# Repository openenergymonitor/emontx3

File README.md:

# emonTx V3.4.x

## Documentation

- [Overview](https://docs.openenergymonitor.org/emontx3/overview.html)
- [Install Guide](https://docs.openenergymonitor.org/emontx3/install.html)
- [Adding to an existing install](https://docs.openenergymonitor.org/emontx3/add.html)
- [3 phase](https://docs.openenergymonitor.org/emontx3/3phase.html)
- [Add ESP8266](https://docs.openenergymonitor.org/emontx3/esp8266.html)
- [Direct Serial](https://docs.openenergymonitor.org/emontx3/direct.html)
- [Configuration](https://docs.openenergymonitor.org/emontx3/configuration.html)
- [Firmware](https://docs.openenergymonitor.org/emontx3/firmware.html)
- [Technical](https://docs.openenergymonitor.org/emontx3/technical.html)

This documentation can also be viewed on github directly [here](docs).

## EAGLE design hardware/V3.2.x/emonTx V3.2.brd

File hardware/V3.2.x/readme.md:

# emonTx 3.2.x

The emonTx v3.2 used the RFu328 module to provide both the ATmega328 and the RFM12B radio module. This was available pre-installed or the emonTx base board. 

## Port Map

*Note: pulse counting on IRQ0, Dig2 rather than IRQ1 Dig3 on the emonTx3.4 

## Firmware

See: [https://github.com/openenergymonitor/emonTxFirmware/tree/master/emonTxV3/RFM/emonTxV3.2 ](https://github.com/openenergymonitor/emonTxFirmware/tree/master/emonTxV3/RFM/emonTxV3.2 )

## RF Connectivity

### RFM12B

To use the RFM12B on the RFu328, a modified version of the JeeLib RF12 library has been created. This is called the [RFu_JeeLib](https://github.com/openenergymonitor/RFu_jeelib) see the GitHub readme for details regarding the modifications. 

The emonTx V3.2 was initially shipped with a wire whip antenna. An SMA antenna could alternatively be added by soldering in the connector on the board. A small wire link was required between the RFu328 and the base board if an RFu328 with headers was used. See [EmonTx_V3_SMA.jpg](img/EmonTx_V3_SMA.jpg) & [EmonTx_V3_SMA_RFu_headers.jpg](img/EmonTx_V3_SMA_RFu_headers.jpg).

Power consumption:

- MCU sleep + RFM12B sleep: 0.034 mA
- MCU running: 7.3mA 
- MCU + LED: 9-10mA
- RFM12B TX ~3ms: 23-28mA

### RF testing

All antennas and RFM12B modules were 433MHz running standard emonTx discrete sampling firmware, transmitting once very 10s.

An RFM69CW receiver provided RSSI readings to enable antenna comparison. The RSSI readings were all lower than normal since the RFM69CW used is an 868MHz module, with an 868MHz antenna, forced via software, to a 433MHz receive frequency.

The emonTxs with the SMA antenna had the RFu328 soldered directly (SMT) to the PCB, the coil and whip antenna had the RFu328 mounted using headers 

## BOM

## Dimensions

Enclosure: extruded aluminium case with acrylic fascia.

**DIN Rail Mount:** Thanks to [@Aquefot](http://twitter.ccom/Aquefot) for contributing a [DIN mount rail fitting CAD design](https://twitter.com/aquefot/status/413708371809026048/photo/1) ready to be 3D printed for the emonTx: [Thingiverse Download](http://www.thingiverse.com/thing:208177) 

## Licence

Creative Commons Attribution-ShareAlike 3.0 Unported License

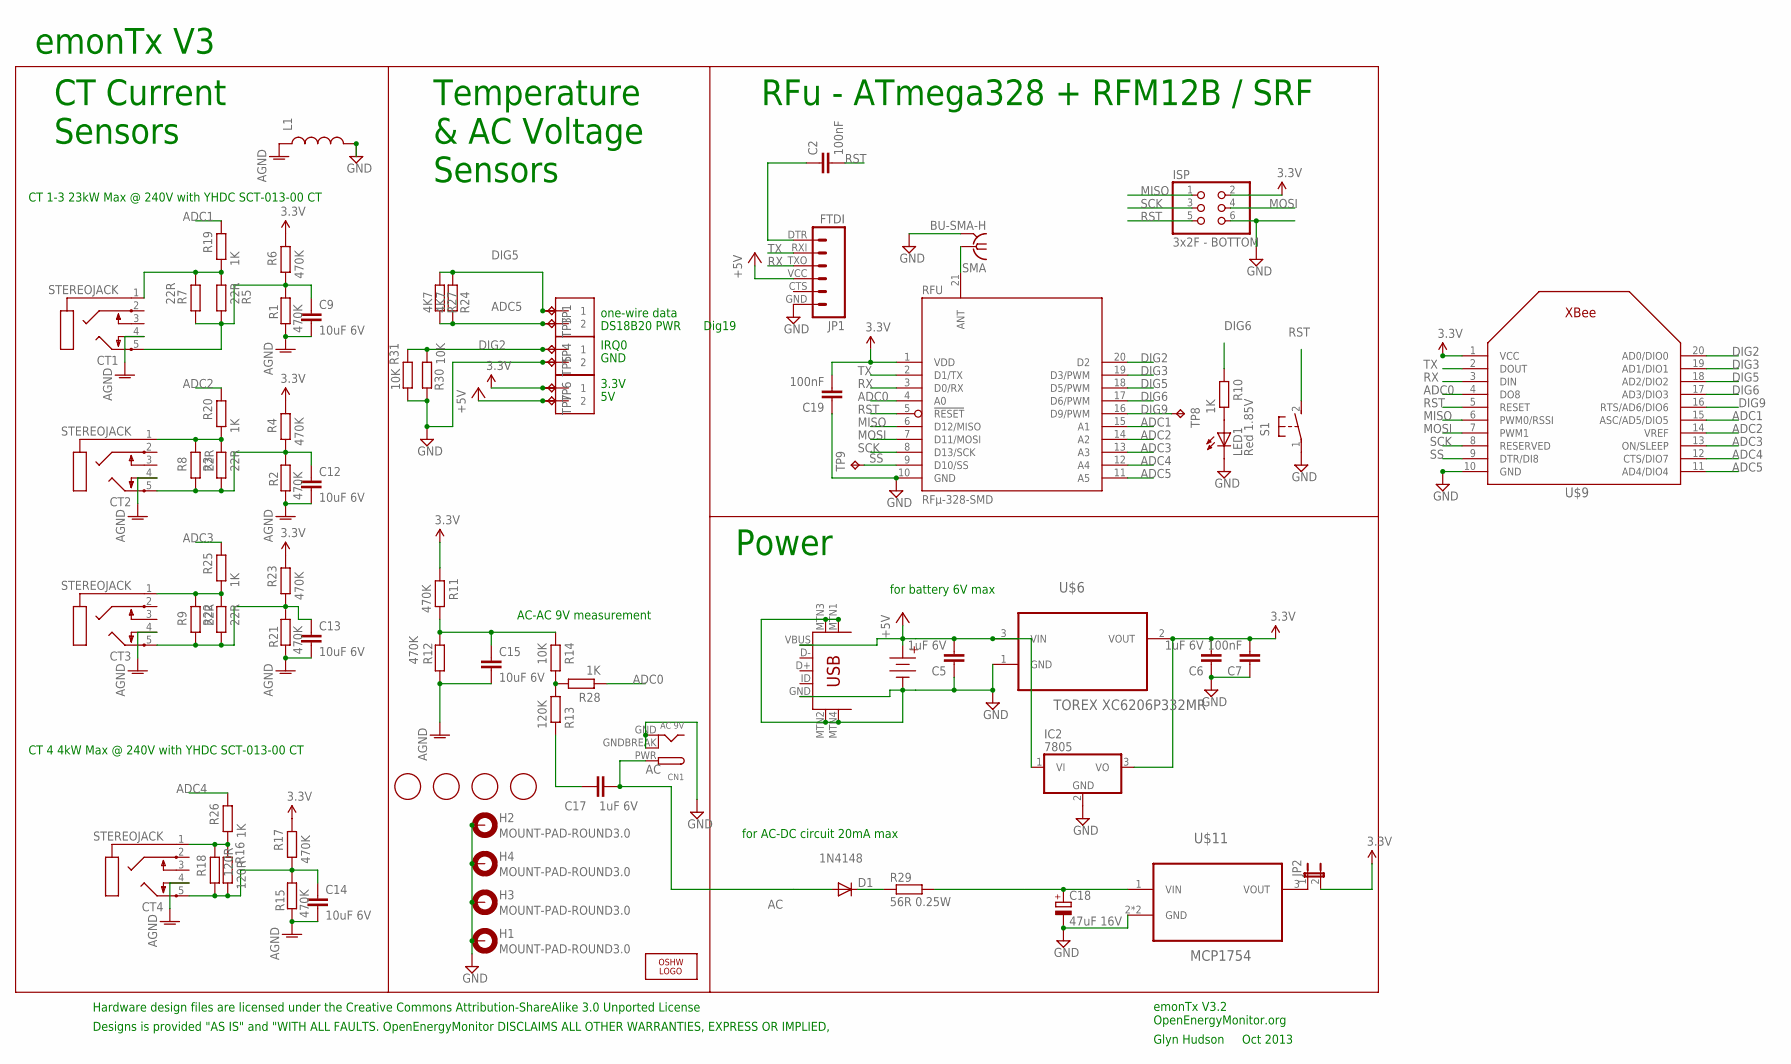
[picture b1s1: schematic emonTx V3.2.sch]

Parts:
C2, C7, C19: 100nF; C0603
C5, C6, C17: 1uF 6V; C0603
C9, C12, C13, C14, C15: 10uF 6V; C0603
C18: 47uF 16V; PANASONIC_D
CN1: AC 9V; DCJACK_2MM_PTH
CT1, CT2, CT3, CT4: STEREOJACK; STX3100
D1: 1N4148; SOD-323
H1, H2, H3, H4: MOUNT-PAD-ROUND3.0; 3,0-PAD
IC2: 7805; TO220V
ISP: 3x2F - BOTTOM; 2X03
J1, J2, J4: 1X2-3.5MM
JP1: FTDI; FTDI_BASIC
JP2: JUMPER-2PTH_LOCK; 1X02_LOCK
L1: INDUCTOR0603; 0603
LED1: Red 1.85V; CHIP-LED0805
LOGO1: OSHW_LOGO_6MILX0200-NT; OSHW_6X200_NOTEXT
R1, R2, R4, R6, R11, R12, R15, R17, R21, R23: 470K; R0603
R3, R5, R22: 22R; 0204/7
R7, R8, R9: 22R; R1206
R10, R19, R20, R25, R26, R28: 1K; R0603
R13: 120K; R0603
R14, R31: 10K; R0603
R16: 120R; 0204/7
R18: 120R; R1206
R24: 4K7; 0204/7
R27: 4K7; R0603
R29: 56R 0.25W; R1206
R30: 10K; 0204/7
RFU: RFµ-328-SMD; RFµ-328-LANDING
S1: 31-XX; B3F-31XX
SMA: BU-SMA-H
TP1, TP3, TP4, TP5, TP6, TP7, TP8, TP9: TPPAD1-13; P1-13
U$1, U$4, U$5, U$7: FIDUCIAL; FIDUCIAL_1MM
U$3: 4.5V; AAA_PCB_HOLDER
U$6: TOREX XC6206P332MR; SOT95P237X112-3N
U$9: XBEE
U$10: USB-MINIB-5PIN; USB-MINIB-CISECO
U$11: MCP1754; SOT89

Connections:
3.3V: C6.2, C7.2, C19.2, IC2.3 (VO), ISP.2, J4.1, JP2.2, R4.2, R6.2, R11.2, R17.2, R23.2, RFU.1 (VDD), TP6.TP, U$6.2 (VOUT), U$9.1 (VCC)
+5V: C5.2, IC2.1 (VI), J4.2, JP1.VCC (4), TP7.TP, U$3.+, U$6.3 (VIN), U$10.VBUS
AC: C17.2, CN1.PWR, D1.2 (A)
ADC0: R28.1, RFU.4 (A0), U$9.4 (DO8)
ADC1: R19.2, RFU.15 (A1), U$9.15 (ASC/AD5/DIO5)
ADC2: R20.2, RFU.14 (A2), U$9.14 (VREF)
ADC3: R25.2, RFU.13 (A3), U$9.13 (ON/SLEEP)
ADC4: R26.2, RFU.12 (A4), U$9.12 (CTS/DIO7)
ADC5: J2.2, R24.2, R27.2, RFU.11 (A5), TP3.TP, U$9.11 (AD4/DIO4)
AGND: C9.2, C12.2, C13.2, C14.2, C15.2, CT1.4, CT2.4, CT3.4, CT4.4, L1.1, R1.2, R2.2, R12.1, R15.2, R21.2
DIG2: J1.1, R30.1, R31.1, RFU.20 (D2), TP4.TP, U$9.20 (AD0/DIO0)
DIG3: RFU.19 (D3/PWM), U$9.19 (AD1/DIO1)
DIG5: J2.1, R24.1, R27.1, RFU.18 (D5/PWM), TP1.TP, U$9.18 (AD2/DIO2)
DIG6: R10.2, RFU.17 (D6/PWM), U$9.17 (AD3/DIO3)
DIG9: RFU.16 (D9/PWM), TP8.TP, U$9.16 (RTS/AD6/DIO6)
GND: C5.1, C6.1, C7.1, C18.-, C19.1, CN1.GND, CN1.GNDBREAK, H1.B3,0, H2.B3,0, H3.B3,0, H4.B3,0, IC2.2 (GND), ISP.6, J1.2, JP1.GND (6), L1.2, LED1.C, R30.2, R31.2, RFU.10 (GND), S1.1, SMA.2, SMA.3 (2), SMA.4 (2), SMA.5 (2), TP5.TP, U$3.-, U$6.1 (GND), U$9.10 (GND), U$10.GND, U$10.MTN1 (MTN2), U$10.MTN2 (MTN3), U$10.MTN3 (MTN1), U$10.MTN4, U$11.2 (GND), U$11.2.1 (GND)
MISO: ISP.1, RFU.6 (D12/MISO), U$9.6 (PWM0/RSSI)
MOSI: ISP.4, RFU.7 (D11/MOSI), U$9.7 (PWM1)
unnamed: CT1.1, R5.2, R7.2, R19.1
unnamed: C13.1, CT3.5, R9.1, R21.1, R22.1, R23.1
unnamed: R13.2, R14.1, R28.2
unnamed: JP2.1, U$11.3 (VOUT)
unnamed: C18.+, R29.2, U$11.1 (VIN)
unnamed: C17.1, R13.1
unnamed: CT4.1, R16.2, R18.2, R26.1
unnamed: C2.1, JP1.DTR (1)
unnamed: CT2.1, R3.2, R8.2, R20.1
unnamed: RFU.21 (ANT), SMA.1
unnamed: D1.1 (C), R29.1
unnamed: CT3.1, R9.2, R22.2, R25.1
unnamed: C12.1, CT2.5, R2.1, R3.1, R4.1, R8.1
unnamed: C15.1, R11.1, R12.2, R14.2
unnamed: C14.1, CT4.5, R15.1, R16.1, R17.1, R18.1
unnamed: C9.1, CT1.5, R1.1, R5.1, R6.1, R7.1
unnamed: LED1.A, R10.1
RST: C2.2, ISP.5, RFU.5 (!RESET), S1.2 (S), U$9.5 (RESET)
RX: JP1.TXO (3), RFU.3 (D0/RX), U$9.3 (DIN)
SCK: ISP.3, RFU.8 (D13/SCK), U$9.8 (RESERVED)
SS: RFU.9 (D10/SS), TP9.TP, U$9.9 (DTR/DI8)
TX: JP1.RXI (2), RFU.2 (D1/TX), U$9.2 (DOUT)

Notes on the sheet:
AC-AC 9V measurement
emonTx V3.2 OpenEnergyMonitor.org
Glyn Hudson Oct 2013
CT 4 4kW Max @ 240V with YHDC SCT-013-00 CT
CT 1-3 23kW Max @ 240V with YHDC SCT-013-00 CT
for battery 6V max
for AC-DC circuit 20mA max
Dig19
Power
RFu - ATmega328 + RFM12B / SRF
CT Current Sensors
Temperature & AC Voltage Sensors
Designs is provided "AS IS" and "WITH ALL FAULTS. OpenEnergyMonitor DISCLAIMS ALL OTHER WARRANTIES, EXPRESS OR IMPLIED,
Hardware design files are licensed under the Creative Commons Attribution-ShareAlike 3.0 Unported License
emonTx V3
DS18B20 PWR
one-wire data
IRQ0
GND
3.3V

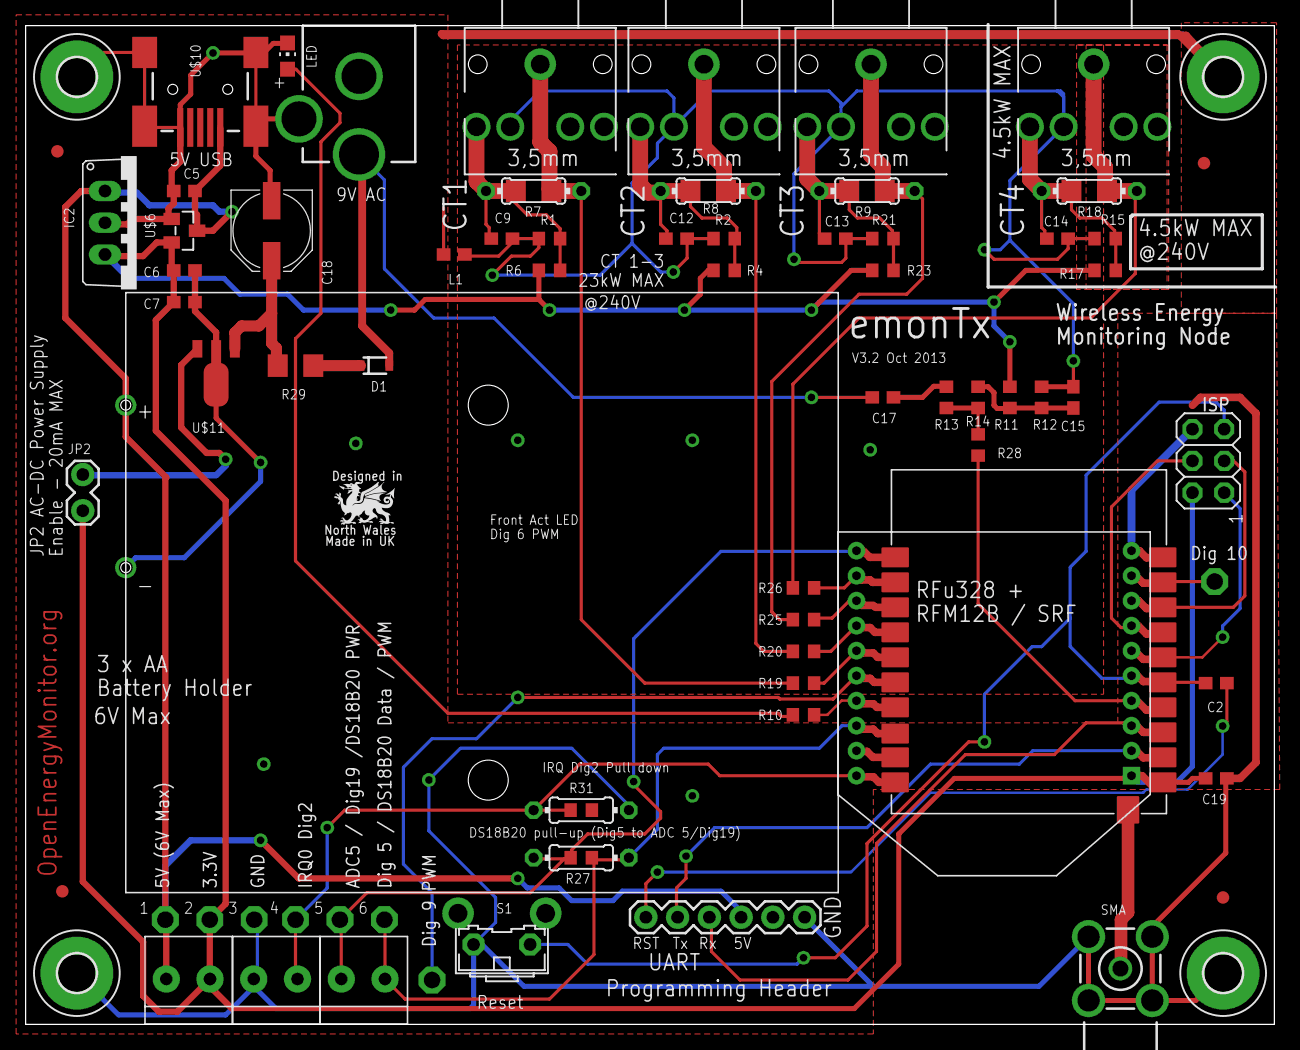
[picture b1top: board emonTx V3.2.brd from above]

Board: 2 copper layers, 99.9 x 79.9 mm, 83 parts (1 on the bottom side), 40 nets.

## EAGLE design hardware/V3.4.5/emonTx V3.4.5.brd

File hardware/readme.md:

# emonTx V3.4

The emonTx V3.4 is the latest generation of the open-source hardware Arduino compatiable emonTx low power wireless energy monitoring node. The unit has been totally re-designed using surface mount (SMT) electronics to enable automated pre-assembled manufacture here in the UK.

## Hardware change log

### V3.4.5 

*Not yet released as of April 2021*

PCB changes
- Remove MLF ATmega footprint to avoid solder bridges during reflow
- Fix rear silkscreen version number
- Improve via spacing 

BOM changes
- Update R13 & R14 from 1% to 0.5% tolerance
- Switch to LDK320ADU33R LDO for higher 18V input voltage
- Remove battery holder from BOM 
- Revert to 4x 3.5mm black CT sockets due to procurement issues for differnet colour sockets
- Moved TSV diodes from ESD5Z3.3T1G to UCLAMP3301H to procurement issues 

### V3.4.4 

Minor PCB changes:

- fix overlayed double via
- Add protection ring for top-right fiducial

### V3.4.3

**Shipping March/April 2018 onwards**

- Identifiable with blue CT4 jackplug socket (mostly)
- Add extra UART header with Rx/Tx swap-over for easy ESP connection
- Increase  reservoir capacitor of AC-DC circuit C18 16uF to 100uF to allow for greater peak power consumption of RFM69CW (compared to RFM12B)
- Change Burden resistors R7, R8, R9 (22R) from 1% to 0.5% tolerance  to increase accuracy. Wanted to change to 0.1% but unable to source
- Changed Burden resistor R18 (120R) from 1 % to 0.1%
- Change all 470K resistors from 1% to 0.1% (R1, R2, R4, R6, R11, R12, R15, R17, R21, R23, R27, R30)
- Changed CT4 jack plug socket to blue colour to indicate low power high accuracy channel

Live BOM: https://octopart.com/bom-tool/xiwE7CiN

#### V3.4.2

**Aug 2016**

- Same BOM as V3.4.1
- Increase mini USB location pin holes from 0.8mm to 0.9mm

#### 3.4.1 Mar 2015

- lots of via GND links around GND plane - make sure ant has best GND plane possible
- make sure antenna has got GND plane under ant PCB trace
- pull top gnd plane in around RFM69CW module and rear GND plan to cover whole undersided
- Get rid of unused L1
- Move D2 location to not be under battery holder
- Correct terminal block silkscreen
- Disconnect RJ45 pin 1 and 3 from GND, stop power rail short if ethernet cable is connected by mistake

#### V3.4

- More FTDI connection bit to the left
- Increase pads for DIP switch
- Add TVS diodes, CT input protection

### V3.3

- ATmega328 on-board
- Edge SMA Antenna
- Non plate through mounting pads to eliminate interference through enclosure
- RJ45 DS18B20 temperature sensor
- 3 x AA Battery monitor on ADC7
- DIP Switch on Dig8 and Dig9 for Node ID selection
- RFM69CW compatible with SEL line pull-up resistor
- Pulse counting / terminal block IRQ changed from D2 IRQ0 to D3 IRQ1 since RFM12B now uses IRQ0
- Changed MCP1700 3.3V regulator to MCP1702 3.3V regulator to allow for powering from higher voltages (12V max) over RJ45

***

## Links

- [Purchase](http://shop.openenergymonitor.com/emontx-v3/)

- [User Guide](https://guide.openenergymonitor.org/setup/emontx)

***

### Schematic

### Board

## Portmap

### Open Hardware

Hardware designs (schematics and CAD) files are licensed under the [Creative Commons Attribution-ShareAlike 3.0 Unported License](http://creativecommons.org/licenses/by-sa/3.0/) and follow the terms of the [OSHW (Open-source hardware) Statement of Principles 1.0.](http://freedomdefined.org/OSHW)

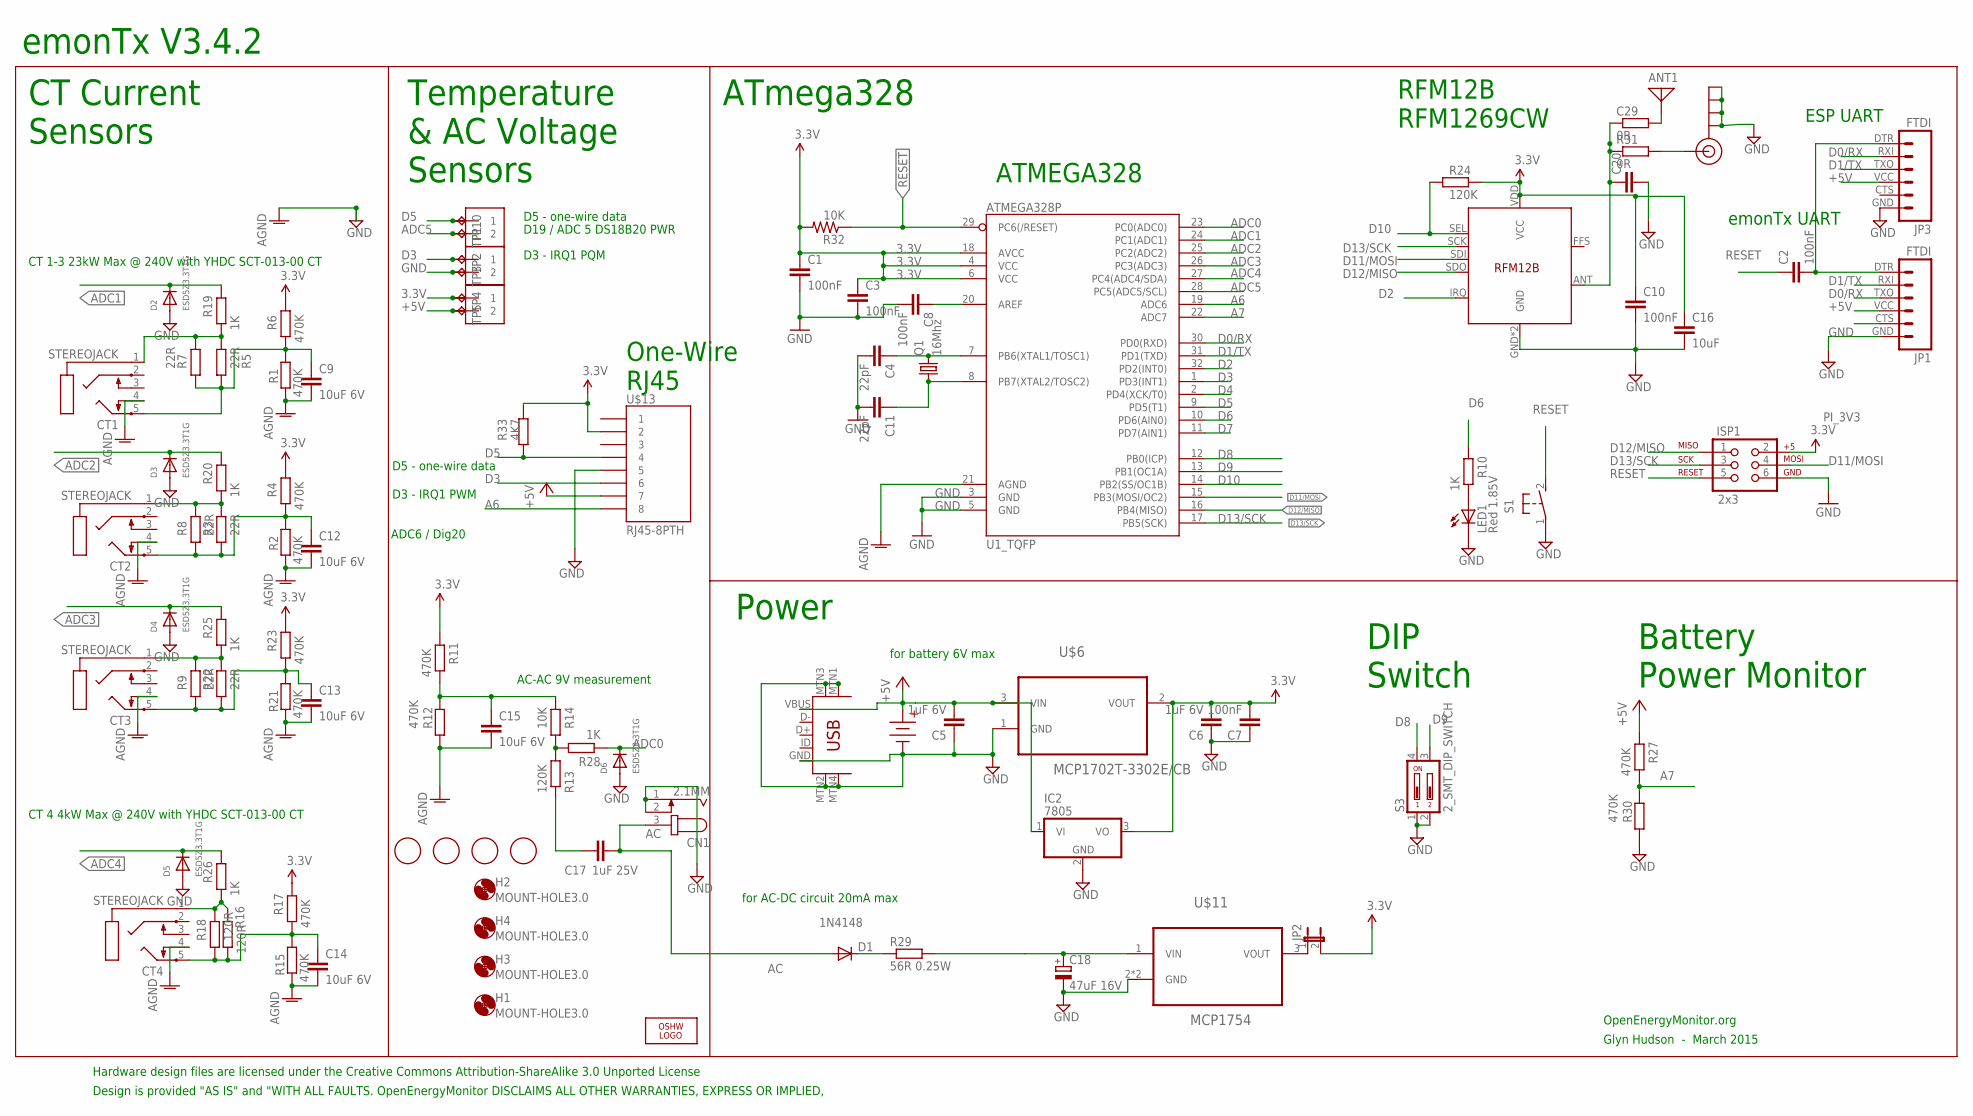
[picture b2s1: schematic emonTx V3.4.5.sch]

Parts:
ANT1: ANTENNA; PAD-01
C1, C2, C3, C7, C8, C10: 100nF; C0603
C4, C11: 22pF; C0603
C5, C6: 1uF 6V; C0603
C9, C12, C13, C14, C15: 10uF 6V; C0603
C16: 10uF; C0603
C17: 1uF 25V; C0603
C18: 47uF 16V; PANASONIC_D
C20: ant tune?; C0603
C29: 0R; R0603
CN1: 2.1MM; SPC4077
CT1, CT2, CT3, CT4: STEREOJACK; STX3100
D1: 1N4148; SOD-323
D2, D3, D4, D5, D6: ESD5Z3.3T1G; SOD-523
H1, H2, H3, H4: MOUNT-HOLE3.0; 3,0
IC2: 7805; TO220V
ISP1: 2x3; 2X3
J3, J5, J6: 1X2-3.5MM
J$1: SMA_EDGE; SMA-EDGE
JP1, JP3: FTDI; FTDI_BASIC
JP2: JUMPER-2PTH_LOCK; 1X02_LOCK
LED1: Red 1.85V; CHIP-LED0805
LOGO1: OSHW_LOGO_6MILX0200-NT; OSHW_6X200_NOTEXT
Q1: 16Mhz; HC49UP
R1, R2, R4, R6, R11, R12, R15, R17, R21, R23, R27, R30: 470K; R0603
R3, R5, R22: 22R; 0204/7
R7, R8, R9: 22R; R1206
R10, R19, R20, R25, R26, R28: 1K; R0603
R13, R24: 120K; R0603
R14, R32: 10K; R0603
R16: 120R; 0204/7
R18: 120R; R1206
R29: 56R 0.25W; R1206
R31: 0R; R0603
R33: 4K7; R0603
S1: 31-XX; B3F-31XX
S3: 2_SMT_DIP_SWITCH; DIP_SWITCH_SMT
TP1, TP2, TP3, TP4, TP5, TP10: TPPAD1-13; P1-13
U1_TQFP: ATMEGA328P; TQFP32-08
U$1, U$4, U$5, U$7: FIDUCIAL; FIDUCIAL_1MM
U$3: 4.5V; AAA_PCB_HOLDER
U$6: MCP1702T-3302E/CB; SOT95P237X112-3N
U$10: USB-MINIB-5PIN; USB-MINIB-CISECO
U$11: MCP1754; SOT89
U$13: RJ45-8PTH; RJ45-8
U$14: RFM12B

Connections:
3.3V: C1.1, C3.1, C6.2, C7.2, C10.1, C16.1, IC2.3 (VO), ISP1.2, J6.1, JP2.2, R4.2, R6.2, R11.2, R17.2, R23.2, R24.2, R32.2, R33.1, TP4.TP, U1_TQFP.4 (VCC), U1_TQFP.6 (VCC), U1_TQFP.18 (AVCC), U$6.2 (VOUT), U$13.2, U$14.VDD (VCC)
+5V: C5.2, IC2.1 (VI), J6.2, JP1.VCC (4), JP3.VCC (4), R27.2, TP5.TP, U$3.+, U$6.3 (VIN), U$10.VBUS, U$13.7
A6: U1_TQFP.19 (ADC6), U$13.8
A7: R27.1, R30.2, U1_TQFP.22 (ADC7)
AC: C17.2, CN1.3, D1.2 (A)
ADC0: D6.K (C), R28.1, U1_TQFP.23 (PC0(ADC0))
ADC1: D2.K (C), R19.2, U1_TQFP.24 (PC1(ADC1))
ADC2: D3.K (C), R20.2, U1_TQFP.25 (PC2(ADC2))
ADC3: D4.K (C), R25.2, U1_TQFP.26 (PC3(ADC3))
ADC4: D5.K (C), R26.2, U1_TQFP.27 (PC4(ADC4/SDA))
ADC5: J3.2, TP1.TP, U1_TQFP.28 (PC5(ADC5/SCL))
AGND: C9.2, C12.2, C13.2, C14.2, C15.2, CT1.4, CT2.4, CT3.4, CT4.4, R1.2, R2.2, R12.1, R15.2, R21.2, U1_TQFP.21 (AGND)
D0/RX: JP1.TXO (3), JP3.RXI (2), U1_TQFP.30 (PD0(RXD))
D1/TX: JP1.RXI (2), JP3.TXO (3), U1_TQFP.31 (PD1(TXD))
D2: U1_TQFP.32 (PD2(INT0)), U$14.IRQ
D3: J5.1, TP2.TP, U1_TQFP.1 (PD3(INT1)), U$13.6
D4: U1_TQFP.2 (PD4(XCK/T0))
D5: J3.1, R33.2, TP10.TP, U1_TQFP.9 (PD5(T1)), U$13.4
D6: R10.2, U1_TQFP.10 (PD6(AIN0))
D7: U1_TQFP.11 (PD7(AIN1))
D8: S3.4, U1_TQFP.12 (PB0(ICP))
D9: S3.3, U1_TQFP.13 (PB1(OC1A))
D10: R24.1, U1_TQFP.14 (PB2(SS/OC1B)), U$14.SEL
D11/MOSI: ISP1.4, U1_TQFP.15 (PB3(MOSI/OC2)), U$14.SDI
D12/MISO: ISP1.1, U1_TQFP.16 (PB4(MISO)), U$14.SDO
D13/SCK: ISP1.3, U1_TQFP.17 (PB5(SCK)), U$14.SCK
DIG1: C20.1, C29.1, R31.1, U$14.ANT
GND: C1.2, C3.2, C4.2, C5.1, C6.1, C7.1, C8.2, C10.2, C11.2, C16.2, C18.-, C20.2, CN1.1, CN1.2, D2.A, D3.A, D4.A, D5.A, D6.A, IC2.2 (GND), ISP1.6, J5.2, J$1.GND@0 (GND), J$1.GND@1 (GND), J$1.GND@2 (GND), J$1.GND@3 (GND), JP1.GND (6), JP3.GND (6), LED1.C, R30.1, S1.1, S3.1, S3.2, TP3.TP, U1_TQFP.3 (GND), U1_TQFP.5 (GND), U$3.-, U$6.1 (GND), U$10.GND, U$10.MTN1 (MTN2), U$10.MTN2 (MTN3), U$10.MTN3 (MTN1), U$10.MTN4, U$11.2 (GND), U$11.2.1 (GND), U$13.5, U$14.GND, U$14.P$12 (GND)
unnamed: C4.1, Q1.2, U1_TQFP.7 (PB6(XTAL1/TOSC1))
unnamed: CT1.1, R5.2, R7.2, R19.1
unnamed: C13.1, CT3.5, R9.1, R21.1, R22.1, R23.1
unnamed: R13.2, R14.1, R28.2
unnamed: JP2.1, U$11.3 (VOUT)
unnamed: C18.+, R29.2, U$11.1 (VIN)
unnamed: C17.1, R13.1
unnamed: CT4.1, R16.2, R18.2, R26.1
unnamed: C11.1, Q1.1, U1_TQFP.8 (PB7(XTAL2/TOSC2))
unnamed: CT2.1, R3.2, R8.2, R20.1
unnamed: ANT1.1, C29.2
unnamed: D1.1 (C), R29.1
unnamed: CT3.1, R9.2, R22.2, R25.1
unnamed: C8.1, U1_TQFP.20 (AREF)
unnamed: C2.2, JP1.DTR (1), JP3.DTR (1)
unnamed: J$1.SIG (SIGNAL), R31.2
unnamed: C12.1, CT2.5, R2.1, R3.1, R4.1, R8.1
unnamed: C15.1, R11.1, R12.2, R14.2
unnamed: C14.1, CT4.5, R15.1, R16.1, R17.1, R18.1
unnamed: C9.1, CT1.5, R1.1, R5.1, R6.1, R7.1
unnamed: LED1.A, R10.1
RESET: C2.1, ISP1.5, R32.1, S1.2 (S), U1_TQFP.29 (PC6(/RESET))

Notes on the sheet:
AC-AC 9V measurement
OpenEnergyMonitor.org
Glyn Hudson - March 2015
CT 4 4kW Max @ 240V with YHDC SCT-013-00 CT
CT 1-3 23kW Max @ 240V with YHDC SCT-013-00 CT
for battery 6V max
for AC-DC circuit 20mA max
Power
ATmega328
CT Current Sensors
Temperature & AC Voltage Sensors
Design is provided "AS IS" and "WITH ALL FAULTS. OpenEnergyMonitor DISCLAIMS ALL OTHER WARRANTIES, EXPRESS OR IMPLIED,
Hardware design files are licensed under the Creative Commons Attribution-ShareAlike 3.0 Unported License
emonTx V3.4.2
D19 / ADC 5 DS18B20 PWR
D5 - one-wire data
D3 - IRQ1 PQM
ATMEGA328
RFM12B RFM1269CW
One-Wire RJ45
D3 - IRQ1 PWM
ADC6 / Dig20
DIP Switch
Battery Power Monitor
ESP UART
emonTx UART

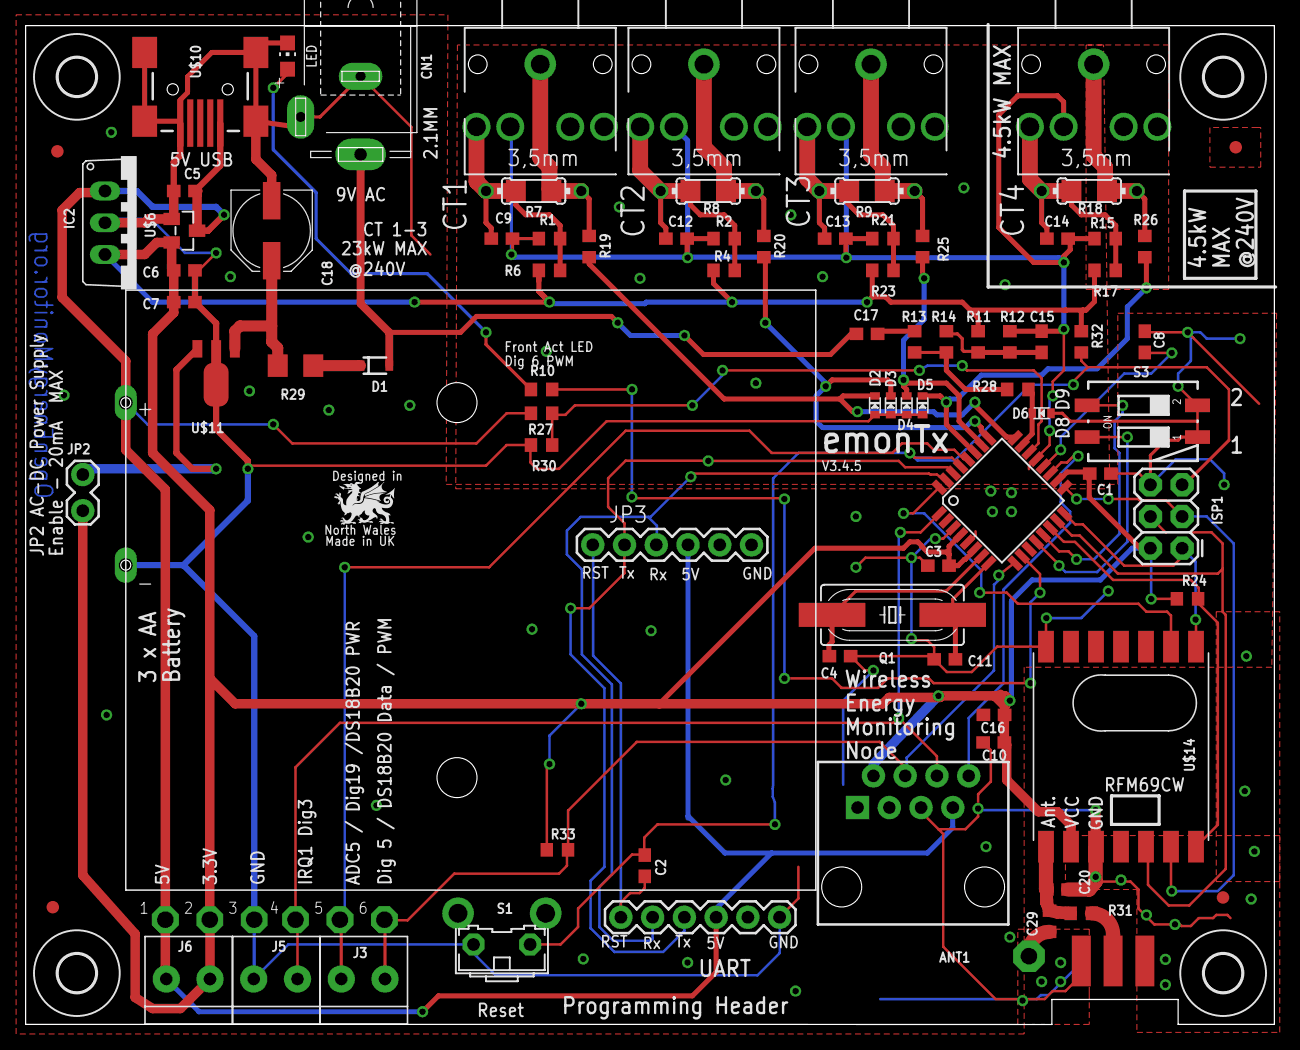
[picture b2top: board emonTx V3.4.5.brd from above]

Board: 2 copper layers, 99.9 x 79.9 mm, 100 parts (1 on the bottom side), 48 nets.

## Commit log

2017-01-22 move emonTx V3.4 hardware & firmware to single repo
2017-01-22 add gerber and enclosure data
2017-01-22 fix travis deployrepo name
2017-01-23 fix deploy gh api key
2017-01-25 change 470k to 0.1%
2017-02-02 set to RFM69CW default
2017-02-15 Fix node ID assignment comments
    https://wiki.openenergymonitor.org/index.php/EmonTx_V3.4#DIP_Switch_Config
2017-02-24 fix USA apparent power readings
2017-02-24 bump version
2017-02-24 fix incorrect serial print of nodeID if set via serial EEPROM and DIP switch
2017-02-24 update changelog
2017-02-27 v2.8 Correct USA voltage to 120V
2017-03-16 Changes to support EmonHubTx3eInterfacer.py and RS485 link.
2017-03-30 correct RMS voltage calc at startup when USA mode is enabled
2017-03-30 bump version v2.9
2017-04-02 fix shop link
2017-04-04 spelling correction
2017-05-07 Pulse counting support on battery power
2017-05-08 Battery powered pulse counting support
2017-06-13 fix space in serial node ID config help text
2017-06-21 Update src.ino
    spelling / grammar corrections
2017-08-08 typo
2017-08-09 custom battery save fw
2017-09-05 add eagle libs
2017-09-05 add description to BOM
2017-09-08 add V2.3.2 HW design
2017-09-22 add V3.4.4 design
2017-09-25 add missing v3.4.3 files
2017-10-05 V3.4.5 TBC
2017-10-06 correct emonhub node decoder for custom fw
2017-10-06 custom name
2018-01-16 V3.0 return zero when no CT conncted
2018-03-09 V3.4.4 is now shipping
2018-03-22 fix PCB revisions
2018-03-22 extract v3.4.4 gerbers
2018-03-22 fix bool compile issue
2018-03-22 add portmap
2018-03-22 wiki note
2018-05-25 bump version 3.2 - both cr & nl
    both cr & nl return prompt on serial monitor
2018-08-24 V3.1 change log update
2018-10-05 Add custom monitor_speed param to env:emontx.
2018-10-26 define monitor baud rate
2018-10-26 correct baud
2018-11-25 Add support for Dallas DS2438 temperature readings used in MS-T temperature sensors
    he DS2438 is commonly used in a lot of ibuttonlink.com sensors which
    are very popular
    https://www.ibuttonlink.com/collections/1-wire-temperature-sensors
    These plug straight into the emontx and are very useful.
    The DS2438 also has other capabilites for measuring DC Voltage and
    current which are not added in this commit. Maybe someday..
2018-11-25 added dependency on arduino-onewire-DS2438
2018-11-25 trying to add dependency on DS2438 libraries again :/
2018-12-17 Update changelog.md
    fix typo
2019-08-05 add ds18b20 testing sketch
2019-08-27 add watchdog reset
2019-08-27 watchdog
2019-09-30 bump version V3.2
2019-09-30 fix serial config
2019-09-30 hardware V3.4.5
2019-10-02 Fix two possible underflows that can generate long delays in loop
    In case the runtime calculated at the end of the loop is greater
    than 9900 ms, the calculated sleeptime underflows. Being it an
    unsigned long, the resulting value would be about 2^32
    milliseconds (about 50 days). This value is used as parameter
    in a delay() function to wait for the next acqusition cycle, if
    AC-AC adapter is used.
2019-10-03 add .pio to gitignore
2019-11-27 add note CM FW as default
2019-12-05 fix factory RFM test sequence V3.3.0
2019-12-05 fix travis build
2019-12-05 fx travis again
2020-08-06 Update src.ino
    Looks like showstring declaration is missing from main src.ino
2020-08-06 fix jeelib
2021-01-05 increase time for temp conversion, required for new batch of RJ45 sensors
2021-01-05 bump version V3.4.0
2021-01-05 update change log
2021-01-08 add DS18B20 test sketch
2021-01-08 organise
2021-01-20 quick test DS18B20
2021-04-07 V3.4.5 hardware, very mintor tweaks for manufacturability
2021-04-07 add not V3.4.5 is not yet in manufacture
2021-04-07 update board image
2021-04-07 add note about CT socket colour
2022-03-10 TSV diode change
2022-11-29 documentation stub
2022-12-02 prelim move of emontx3 docs from guide
2022-12-28 seperate firmware guide and wiki content copied over to technical
2022-12-29 direct serial documentation
2022-12-29 move configuration to own page
2022-12-29 overview page
2022-12-29 burden resistor calculations
2022-12-30 further content from wiki page
2023-01-24 move wiki content
2023-01-25 fix links
2023-02-16 new emonTx3 CM and 3phase firmware with wider radio compatibility
2023-02-16 remove readme
2023-02-16 rename 3phase
2023-02-16 3-phase LowPowerLabs firmware support
2023-02-16 update emontx3.2 CM firmware
2023-02-16 remove submodule
2023-02-16 emontx3.2 cm firmware
2023-02-16 ignore generated hex files
2023-02-16 update firmware documentation page
2023-02-16 update headings
2023-02-16 update serial configuration documentation
2023-02-16 firmware readme
2023-02-16 update 3-phase docs
2023-02-16 disable factory test for low power labs
2023-08-31 Add board files.
2023-09-01 Fix newline handling. Now the code doesn't care if you send \r, \r\n, \n, \n\r
2023-09-03 fix warning and potential crash from array out of bounds error
2023-09-03 I'm using JEELIB_CLASSIC it would seem
2023-09-08 Revert "I'm using JEELIB_CLASSIC it would seem"
    This reverts commit 1710b2c68b60b56d9baa6593dfd9aa2490a91ed3.
2025-10-13 3phase.md: Update links

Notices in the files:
parts and their libraries:
SparkFun-DigitalIC: Licensing: CC v3.0 Share-Alike You are welcome to use this library for commercial purposes.
microbuilder: This work is placed in the public domain, and may be freely used for commercial and non-commercial work with the following conditions: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
